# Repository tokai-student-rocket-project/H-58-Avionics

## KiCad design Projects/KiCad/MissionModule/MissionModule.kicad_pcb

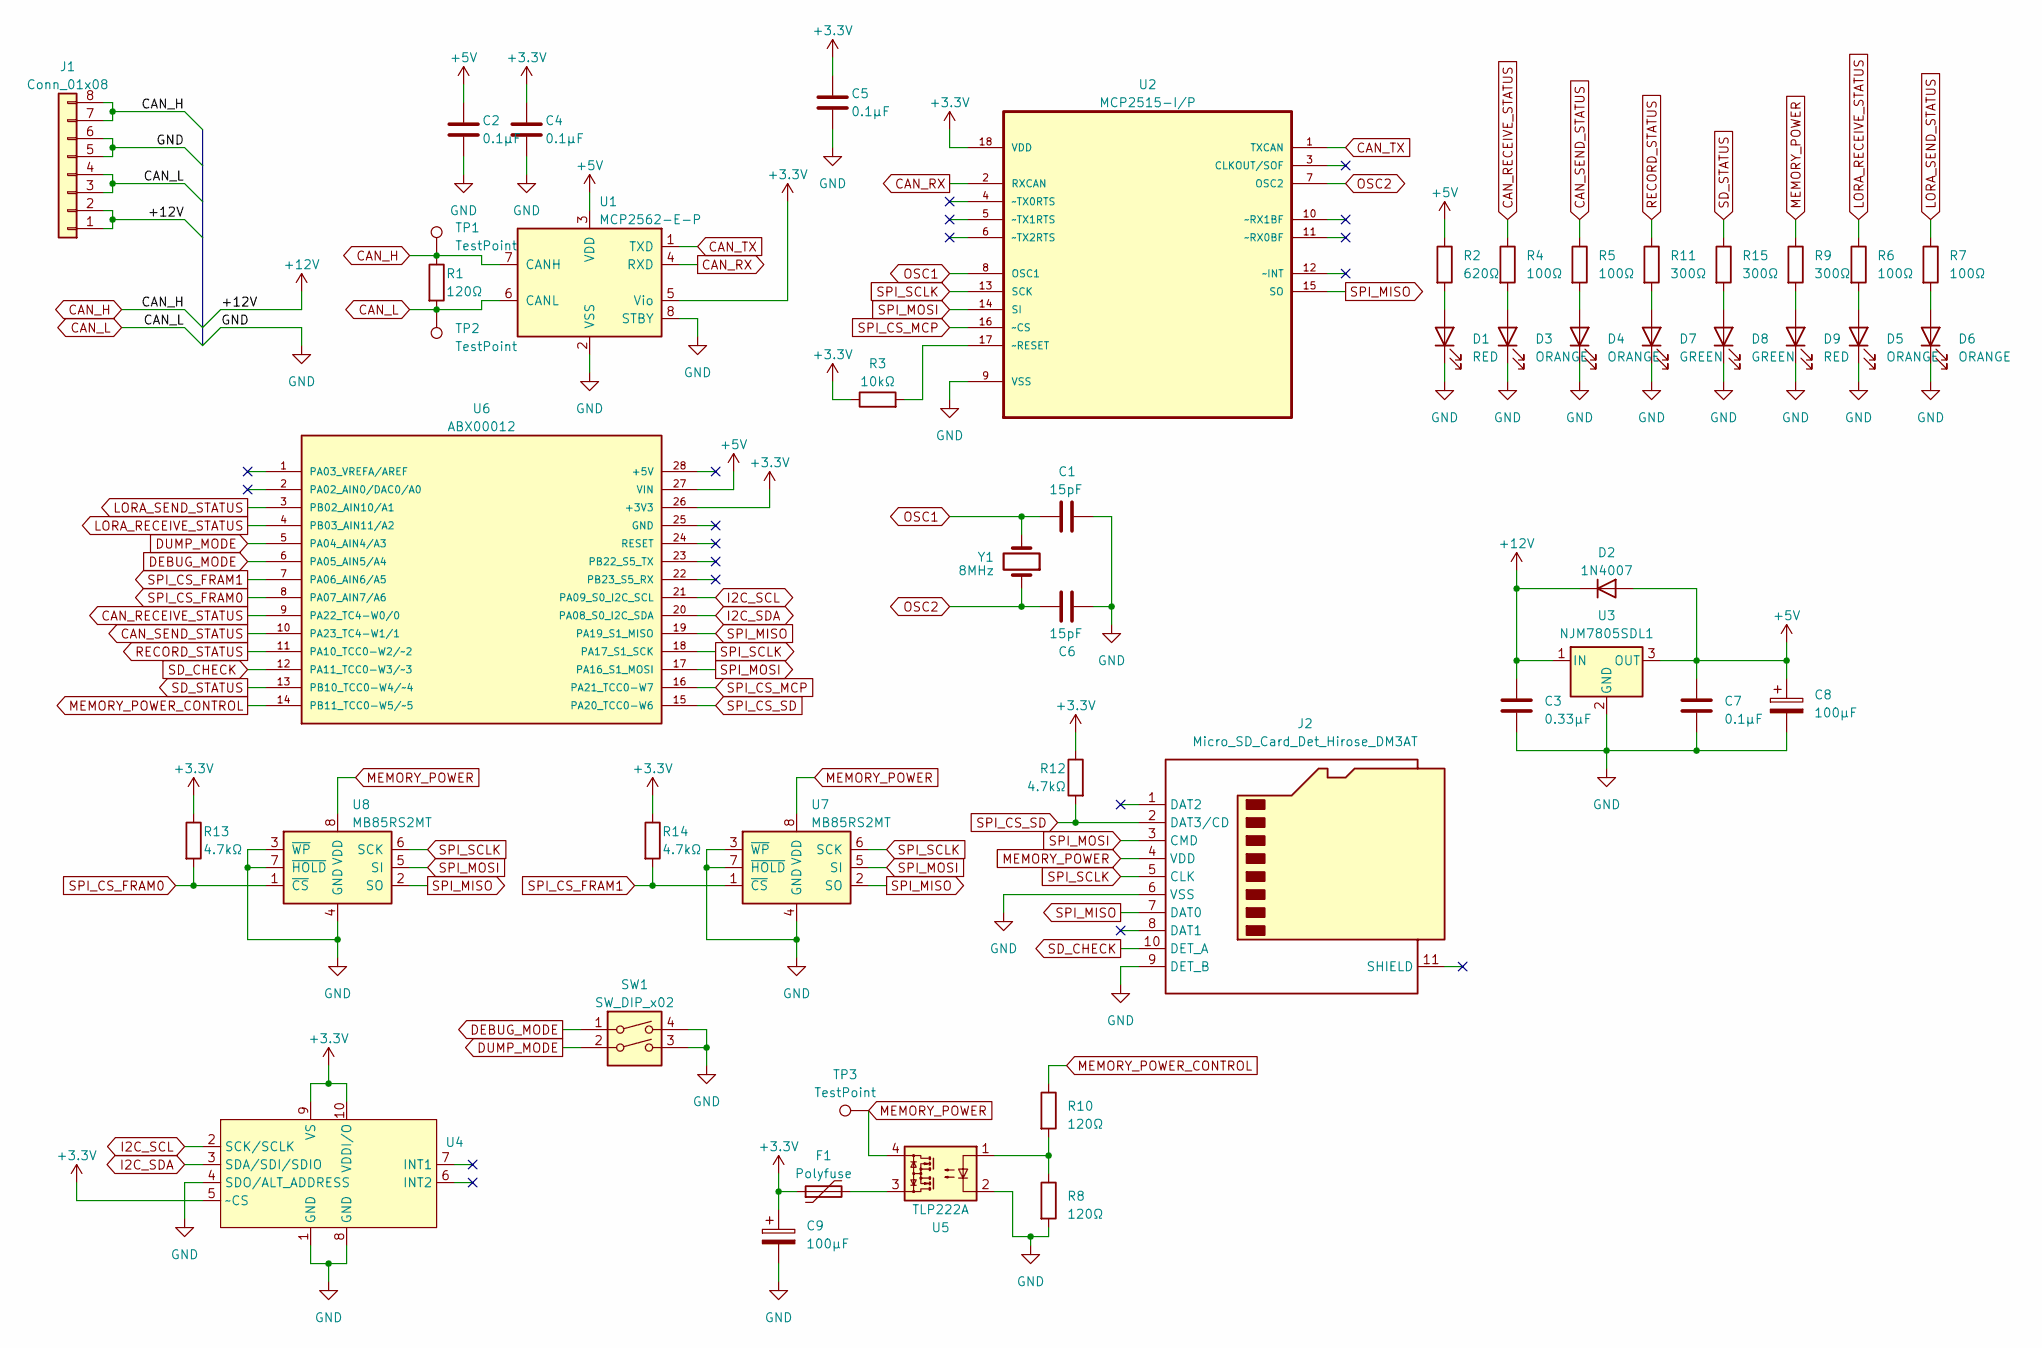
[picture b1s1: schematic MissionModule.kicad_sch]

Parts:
C1, C6: 15pF; C_0603_1608Metric_Pad1.08x0.95mm_HandSolder
C2, C4, C5, C7: 0.1μF; C_0805_2012Metric_Pad1.18x1.45mm_HandSolder
C3: 0.33μF; C_0805_2012Metric_Pad1.18x1.45mm_HandSolder
C8, C9: 100μF; CP_Elec_6.3x7.7
D1, D9: RED; LED_0603_1608Metric_Pad1.05x0.95mm_HandSolder
D2: 1N4007; D_SOD-123F
D3, D4, D5, D6: ORANGE; LED_0603_1608Metric_Pad1.05x0.95mm_HandSolder
D7, D8: GREEN; LED_0603_1608Metric_Pad1.05x0.95mm_HandSolder
F1: Polyfuse; Fuse_1206_3216Metric_Pad1.42x1.75mm_HandSolder
J1: Conn_01x08; Hirose_DF11-8DP-2DSA_2x04_P2.00mm_Vertical
J2: Micro_SD_Card_Det_Hirose_DM3AT; microSD_HC_Hirose_DM3AT-SF-PEJM5
R1, R8, R10: 120Ω; R_0603_1608Metric_Pad0.98x0.95mm_HandSolder
R2: 620Ω; R_0603_1608Metric_Pad0.98x0.95mm_HandSolder
R3: 10kΩ; R_0603_1608Metric_Pad0.98x0.95mm_HandSolder
R4, R5, R6, R7: 100Ω; R_0603_1608Metric_Pad0.98x0.95mm_HandSolder
R9, R11, R15: 300Ω; R_0603_1608Metric_Pad0.98x0.95mm_HandSolder
R12, R13, R14: 4.7kΩ; R_0603_1608Metric_Pad0.98x0.95mm_HandSolder
SW1: SW_DIP_x02; SW_DIP_SPSTx02_Piano_10.8x6.64mm_W7.62mm_P2.54mm
TP1, TP2, TP3: TestPoint; Pin_D1.0mm_L10.0mm
U1: MCP2562-E-P; DIP-8_W7.62mm
U2: MCP2515-I/P; DIP-18_W7.62mm; MPN MCP2515-I/P
U3: NJM7805SDL1; TO-252-2
U4: ADXL375
U5: TLP222A; DIP-4_W7.62mm
U6: ABX00012; ARDUINO_ABX00012; PARTREV 5
U7, U8: MB85RS2MT; DIP-8_W7.62mm
Y1: 8MHz; Crystal_HC49-U_Vertical

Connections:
+3.3V: C4.1, C5.1, C9.1, F1.1, R3.1, R12.1, R13.1, R14.1, U1.5 (Vio), U2.18 (VDD), U4.5 (~CS), U4.9 (VS), U4.10 (VDDI/O), U6.26 (+3V3)
+5V: C2.1, C7.1, C8.1, D2.2 (A), R2.1, U1.3 (VDD), U3.3 (OUT), U6.27 (VIN)
+12V: C3.1, D2.1 (K), J1.1, J1.2, U3.1 (IN)
CAN_H: J1.7, J1.8, R1.1, TP1.1, U1.7 (CANH)
CAN_L: J1.3, J1.4, R1.2, TP2.1, U1.6 (CANL)
CAN_RECEIVE_STATUS: R4.1, U6.9 (PA22_TC4-W0/0)
CAN_RX: U1.4 (RXD), U2.2 (RXCAN)
CAN_SEND_STATUS: R5.1, U6.10 (PA23_TC4-W1/1)
CAN_TX: U1.1 (TXD), U2.1 (TXCAN)
DEBUG_MODE: SW1.1, U6.6 (PA05_AIN5/A4)
DUMP_MODE: SW1.2, U6.5 (PA04_AIN4/A3)
GND: C1.1, C2.2, C3.2, C4.2, C5.2, C6.1, C7.2, C8.2, C9.2, D1.1 (K), D3.1 (K), D4.1 (K), D5.1 (K), D6.1 (K), D7.1 (K), D8.1 (K), D9.1 (K), J1.5, J1.6, J2.6 (VSS), J2.9 (DET_B), R8.2, SW1.3, SW1.4, U1.2 (VSS), U1.8 (STBY), U2.9 (VSS), U3.2 (GND), U4.1 (GND), U4.4 (SDO/ALT_ADDRESS), U4.8 (GND), U5.2, U7.3 (~WP), U7.4 (GND), U7.7 (~HOLD), U8.3 (~WP), U8.4 (GND), U8.7 (~HOLD)
I2C_SCL: U4.2 (SCK/SCLK), U6.21 (PA09_S0_I2C_SCL)
I2C_SDA: U4.3 (SDA/SDI/SDIO), U6.20 (PA08_S0_I2C_SDA)
LORA_RECEIVE_STATUS: R6.1, U6.4 (PB03_AIN11/A2)
LORA_SEND_STATUS: R7.1, U6.3 (PB02_AIN10/A1)
MEMORY_POWER: J2.4 (VDD), R9.1, TP3.1, U5.4, U7.8 (VDD), U8.8 (VDD)
MEMORY_POWER_CONTROL: R10.1, U6.14 (PB11_TCC0-W5/~5)
unnamed: D1.2 (A), R2.2
unnamed: D3.2 (A), R4.2
unnamed: D4.2 (A), R5.2
unnamed: D5.2 (A), R6.2
unnamed: D6.2 (A), R7.2
unnamed: D7.2 (A), R11.2
unnamed: D8.2 (A), R15.2
unnamed: D9.2 (A), R9.2
unnamed: F1.2, U5.3
unnamed: R8.1, R10.2, U5.1
unnamed: R3.2, U2.17 (~RESET)
OSC1: C1.2, U2.8 (OSC1), Y1.2
OSC2: C6.2, U2.7 (OSC2), Y1.1
RECORD_STATUS: R11.1, U6.11 (PA10_TCC0-W2/~2)
SD_CHECK: J2.10 (DET_A), U6.12 (PA11_TCC0-W3/~3)
SD_STATUS: R15.1, U6.13 (PB10_TCC0-W4/~4)
SPI_CS_FRAM0: R13.2, U6.8 (PA07_AIN7/A6), U8.1 (~CS)
SPI_CS_FRAM1: R14.2, U6.7 (PA06_AIN6/A5), U7.1 (~CS)
SPI_CS_MCP: U2.16 (~CS), U6.16 (PA21_TCC0-W7)
SPI_CS_SD: J2.2 (DAT3/CD), R12.2, U6.15 (PA20_TCC0-W6)
SPI_MISO: J2.7 (DAT0), U2.15 (SO), U6.19 (PA19_S1_MISO), U7.2 (SO), U8.2 (SO)
SPI_MOSI: J2.3 (CMD), U2.14 (SI), U6.17 (PA16_S1_MOSI), U7.5 (SI), U8.5 (SI)
SPI_SCLK: J2.5 (CLK), U2.13 (SCK), U6.18 (PA17_S1_SCK), U7.6 (SCK), U8.6 (SCK)

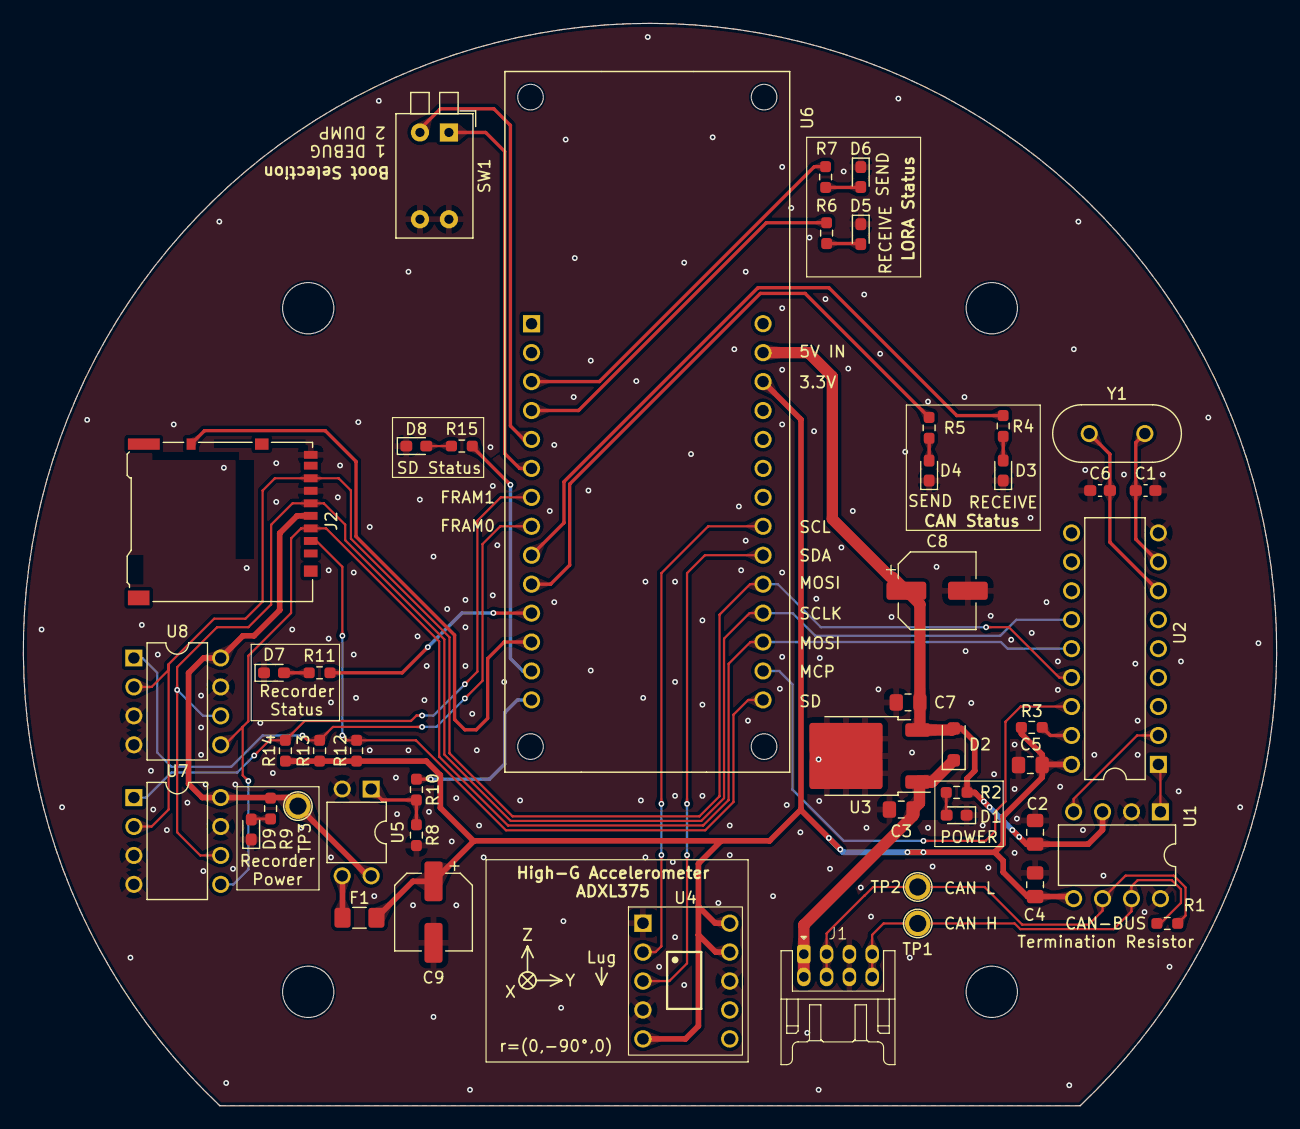
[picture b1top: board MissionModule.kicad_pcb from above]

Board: 2 copper layers, 110.0 x 95.0 mm, 49 parts (0 on the bottom side), 41 nets.

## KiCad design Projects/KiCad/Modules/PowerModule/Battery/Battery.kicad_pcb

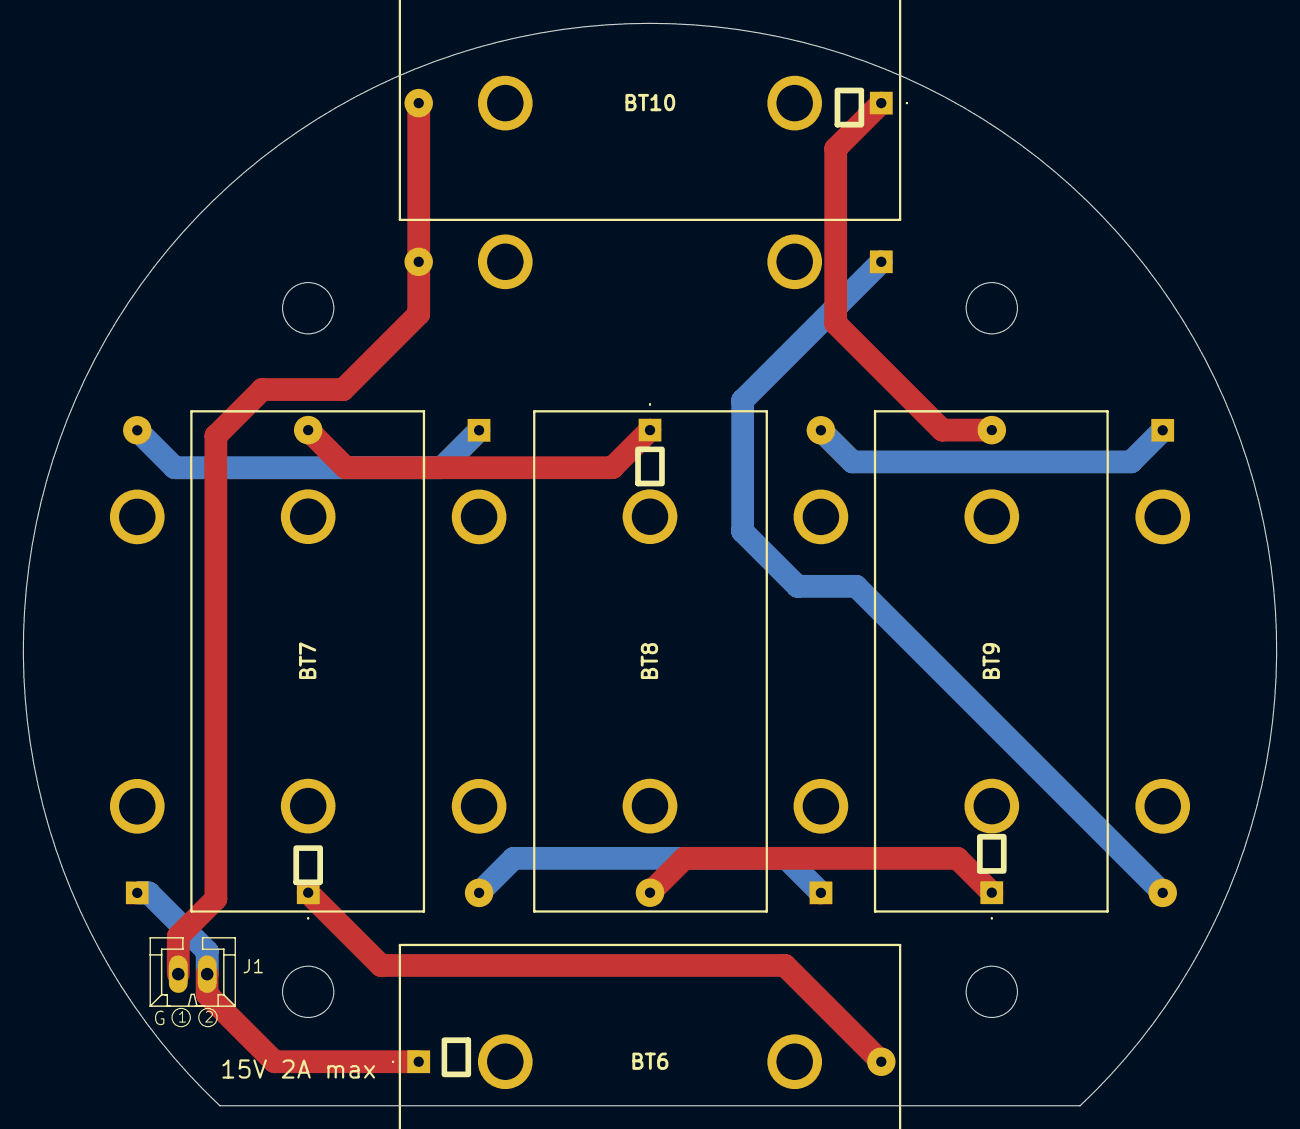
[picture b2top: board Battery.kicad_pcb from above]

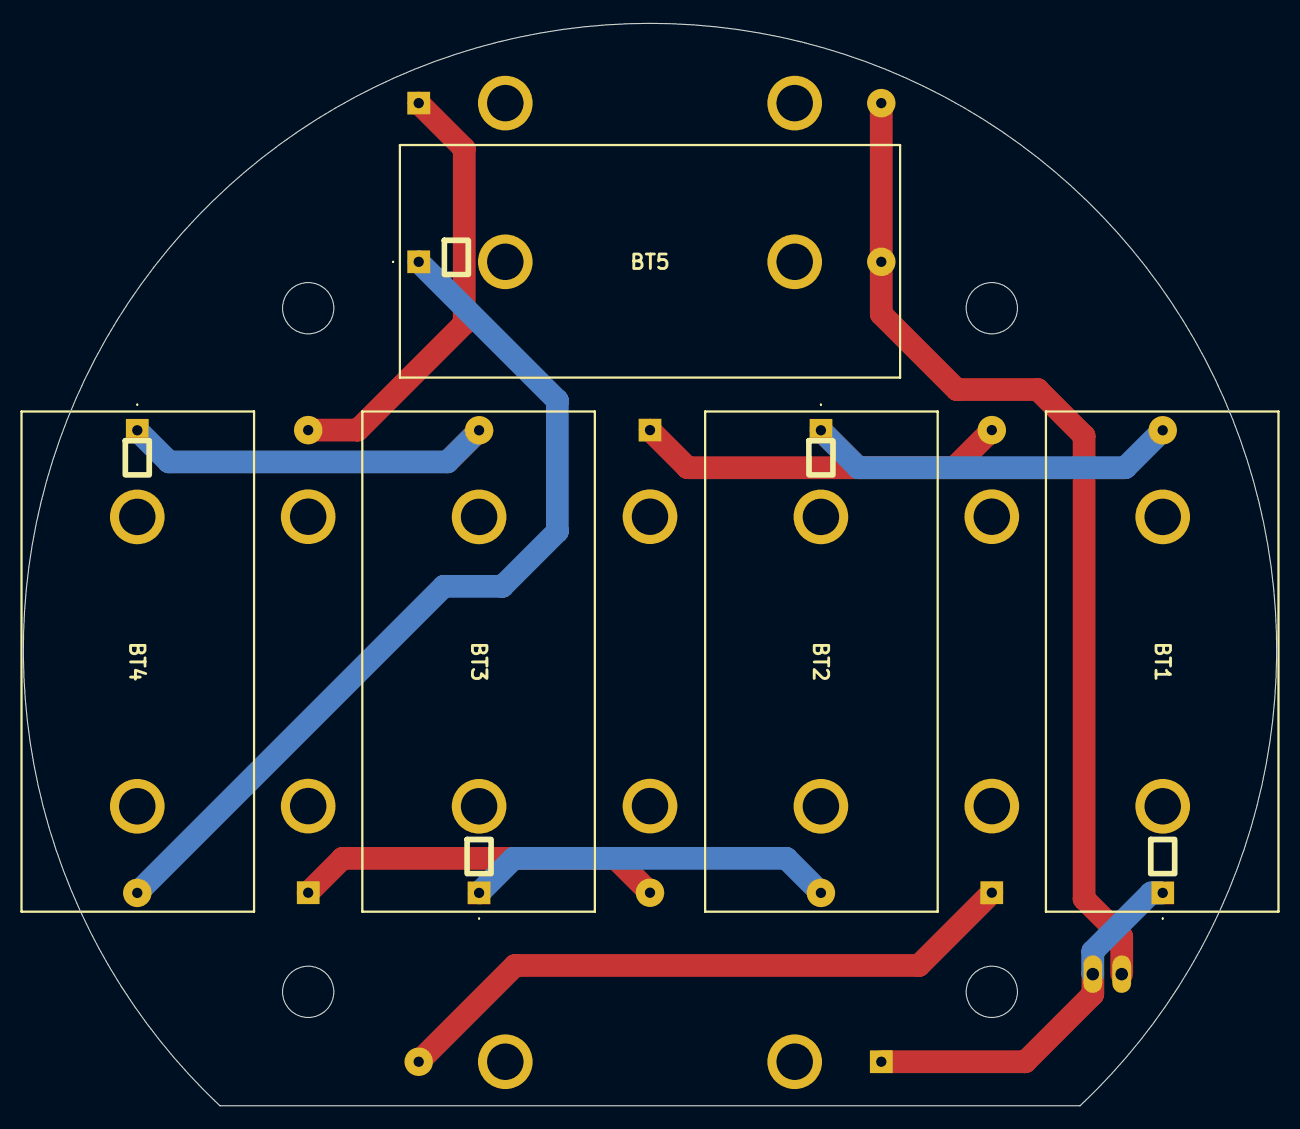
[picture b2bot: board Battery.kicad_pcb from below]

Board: 2 copper layers, 110.0 x 95.0 mm, 11 parts (5 on the bottom side), 10 nets.

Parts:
BT1, BT2, BT3, BT4, BT5, BT6, BT7, BT8, BT9, BT10: Battery_Cell; CR123APC
J1: Conn_01x02_Socket; CONNECTOR_2-STRAIGHT

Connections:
unnamed: BT1.1 (+), BT6.1 (+), J1.2
unnamed: BT1.2 (-), BT2.1 (+)
unnamed: BT2.2 (-), BT3.1 (+)
unnamed: BT3.2 (-), BT4.1 (+)
unnamed: BT4.2 (-), BT5.1 (+)
unnamed: BT6.2 (-), BT7.1 (+)
unnamed: BT7.2 (-), BT8.1 (+)
unnamed: BT8.2 (-), BT9.1 (+)
unnamed: BT9.2 (-), BT10.1 (+)
unnamed: BT5.2 (-), BT10.2 (-), J1.1

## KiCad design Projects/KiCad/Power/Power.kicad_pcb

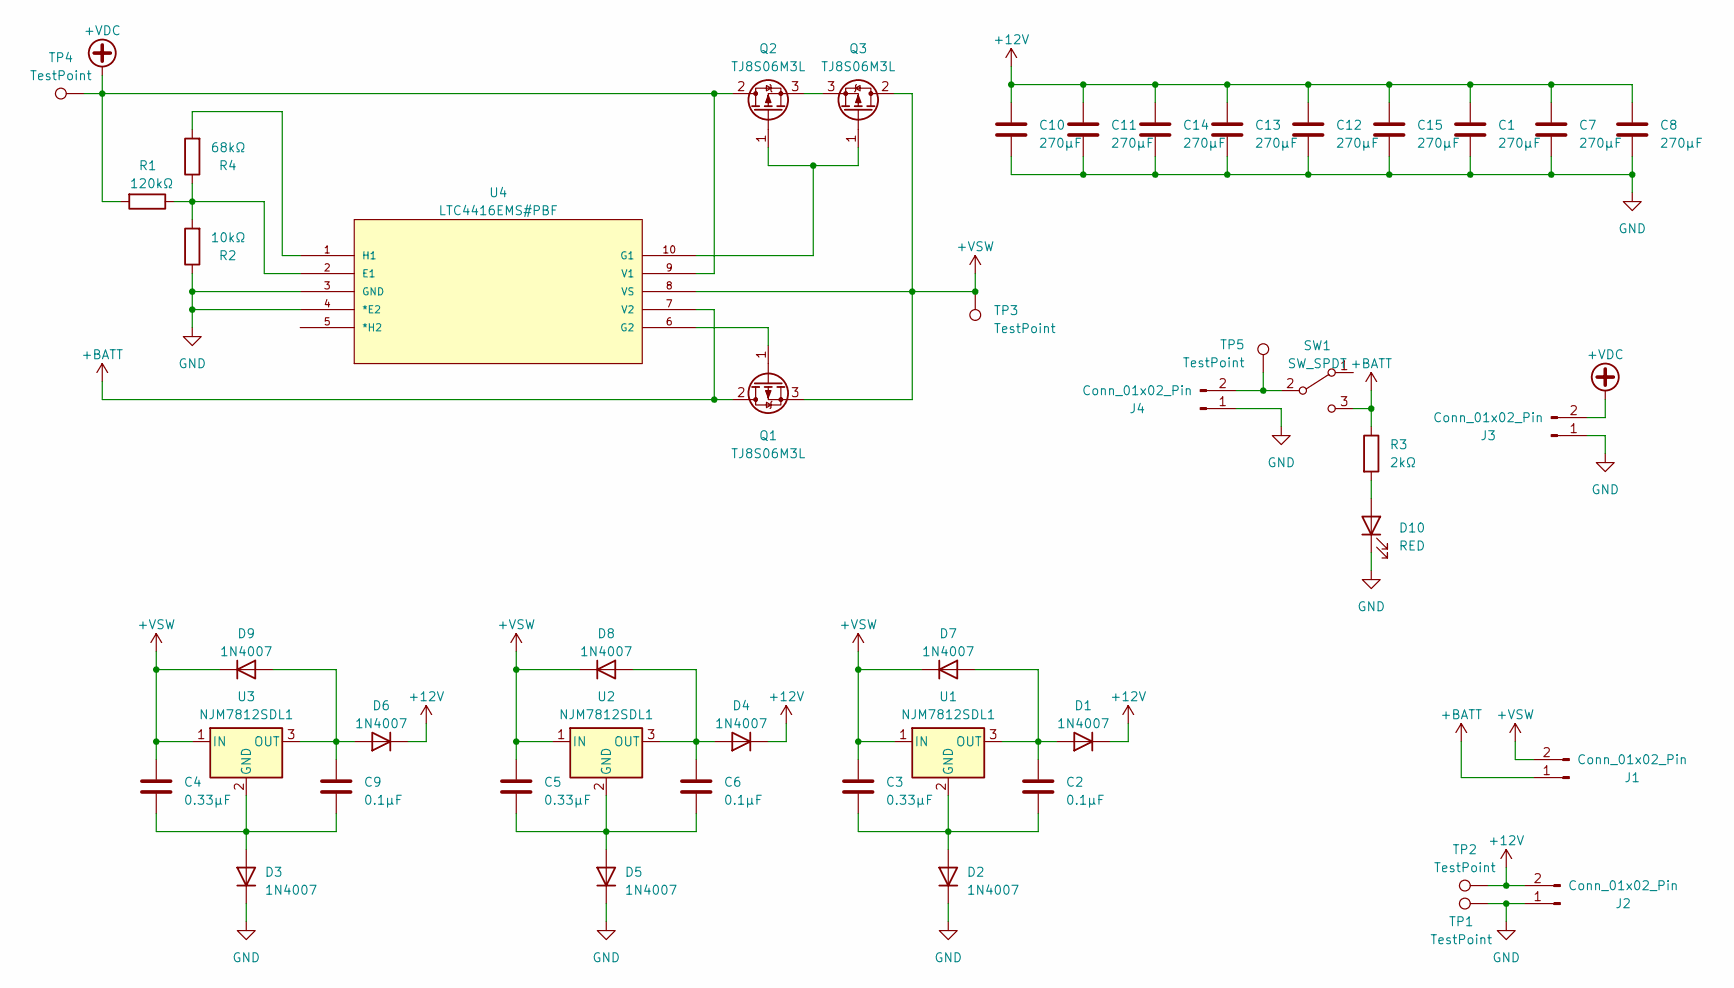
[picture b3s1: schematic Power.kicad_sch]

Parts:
C1, C7, C8, C10, C11, C12, C13, C14, C15: 270μF; CP_Radial_D10.0mm_P3.50mm
C2, C6, C9: 0.1μF; C_0805_2012Metric_Pad1.18x1.45mm_HandSolder
C3, C4, C5: 0.33μF; C_0805_2012Metric_Pad1.18x1.45mm_HandSolder
D1, D2, D3, D4, D5, D6, D7, D8, D9: 1N4007; D_SOD-123F
D10: RED; LED_0603_1608Metric_Pad1.05x0.95mm_HandSolder
J1, J2, J3, J4: Conn_01x02_Pin; Hirose_DF1B
Q1, Q2, Q3: TJ8S06M3L; TO-252-2
R1: 120kΩ; R_0603_1608Metric_Pad0.98x0.95mm_HandSolder
R2: 10kΩ; R_0603_1608Metric_Pad0.98x0.95mm_HandSolder
R3: 2kΩ; R_0603_1608Metric_Pad0.98x0.95mm_HandSolder
R4: 68kΩ; R_0603_1608Metric_Pad0.98x0.95mm_HandSolder
SW1: SW_SPDT; 2MS1T1B4M7QES
TP1, TP2, TP3, TP4, TP5: TestPoint; Pin_D1.0mm_L10.0mm
U1, U2, U3: NJM7812SDL1; TO-252-2
U4: LTC4416EMS#PBF; MSOP-10-1EP_3x3mm_P0.5mm_EP1.73x1.98mm; MANUFACTURER_PART_NUMBER ltc4416ims1

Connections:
+12V: C1.1, C7.1, C8.1, C10.1, C11.1, C12.1, C13.1, C14.1, C15.1, D1.1 (K), D4.1 (K), D6.1 (K), J2.2, TP2.1
+BATT: J1.1, Q1.2 (D), R3.1, SW1.3 (C), U4.7 (V2)
+VDC: J3.2, Q2.2 (D), R1.2, TP4.1, U4.9 (V1)
+VSW: C3.1, C4.1, C5.1, D7.1 (K), D8.1 (K), D9.1 (K), J1.2, Q1.3 (S), Q3.2 (D), TP3.1, U1.1 (IN), U2.1 (IN), U3.1 (IN), U4.8 (VS)
GND: C1.2, C7.2, C8.2, C10.2, C11.2, C12.2, C13.2, C14.2, C15.2, D2.1 (K), D3.1 (K), D5.1 (K), D10.1 (K), J2.1, J3.1, J4.1, R2.1, TP1.1, U4.3 (GND), U4.4 (*E2)
unnamed: C2.1, D1.2 (A), D7.2 (A), U1.3 (OUT)
unnamed: C2.2, C3.2, D2.2 (A), U1.2 (GND)
unnamed: C4.2, C9.2, D3.2 (A), U3.2 (GND)
unnamed: C6.1, D4.2 (A), D8.2 (A), U2.3 (OUT)
unnamed: C5.2, C6.2, D5.2 (A), U2.2 (GND)
unnamed: C9.1, D6.2 (A), D9.2 (A), U3.3 (OUT)
unnamed: D10.2 (A), R3.2
unnamed: J4.2, SW1.2 (B), TP5.1
unnamed: Q1.1 (G), U4.6 (G2)
unnamed: Q2.1 (G), Q3.1 (G), U4.10 (G1)
unnamed: Q2.3 (S), Q3.3 (S)
unnamed: R1.1, R2.2, R4.1, U4.2 (E1)
unnamed: R4.2, U4.1 (H1)

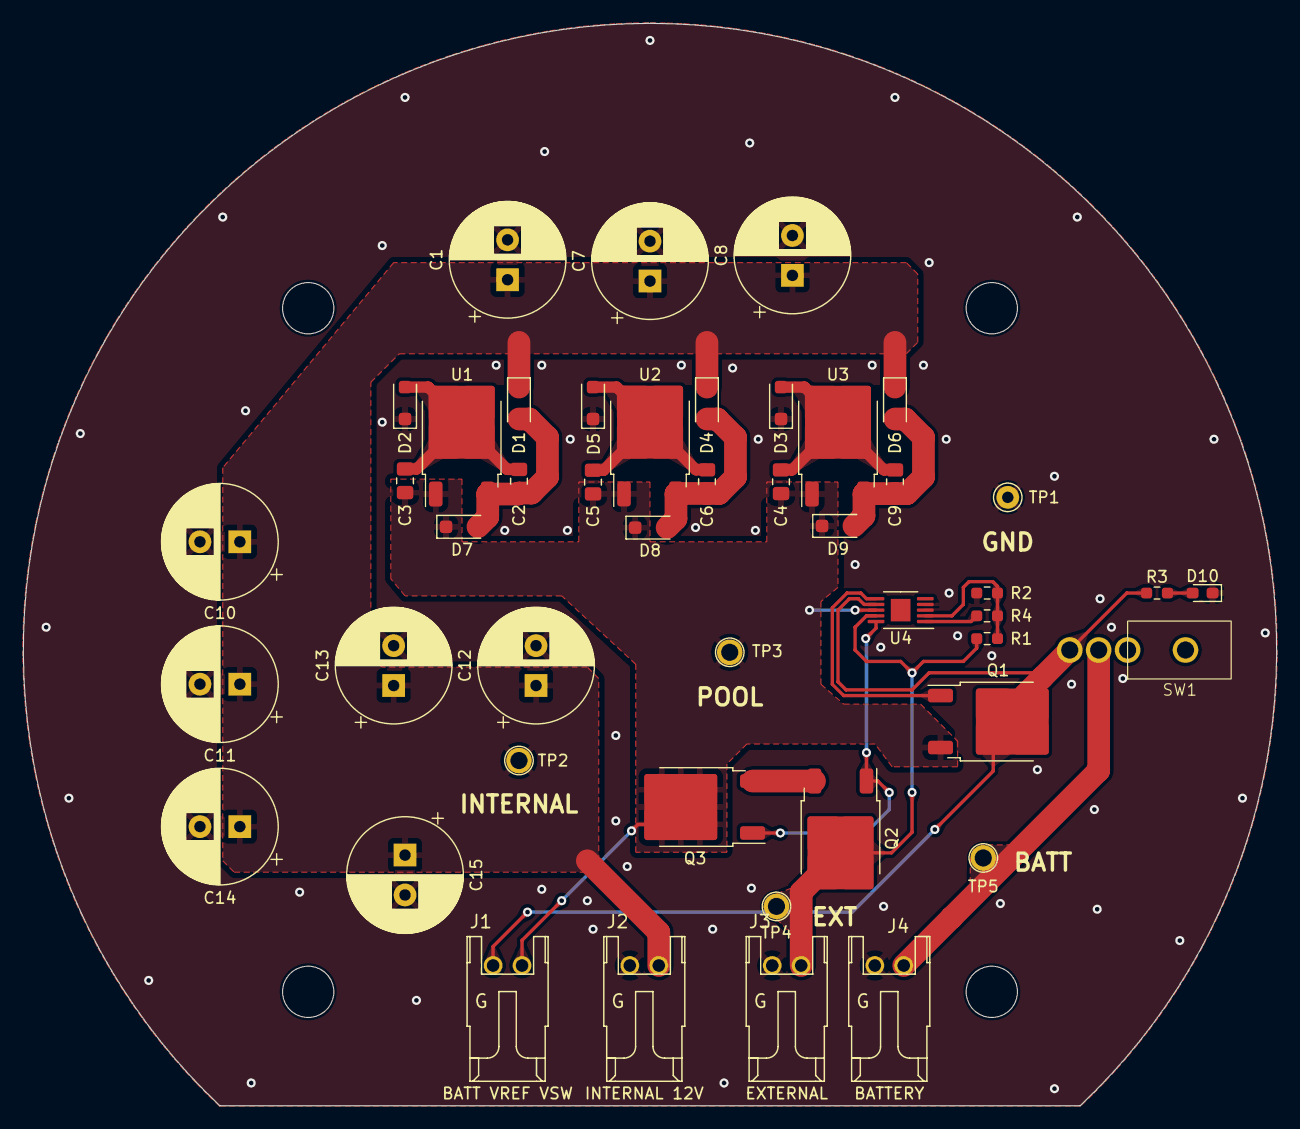
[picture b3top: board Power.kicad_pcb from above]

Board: 2 copper layers, 110.0 x 95.0 mm, 46 parts (0 on the bottom side), 18 nets.
